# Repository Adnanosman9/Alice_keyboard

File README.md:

# Alvonomic

### This is an alice style keyboard

It has 65 keys

## Key Features
* Brain - It has a pico as braim as it has enough pins for a larg keybord
* Firmware - It usws QMK firmware built with QMK MSYS
* Keys - It has 65 keys (32 on left and 33 on right)

# Layout

This keyboard is built in Alice style. So, it has 2 sides. 

The layout was built using [Keyboard Laoyt Editor](https://www.keyboard-layout-editor.com/#/)

Compulsory sketch for this layout was geenrated with [swillkb](http://builder.swillkb.com/)

# The board

The board schematic and PCB is made in KiCAD 10. 

Tried to keep all files minimalistic and easy to understand. 

## Schematic

The schematic has all the details you need to understand it. 

Here is also a pico diagram if u need

## PCB

The board is made in PCB editor of KiCAD

The layout is arranged using [KLE Placer](https://github.com/zykrah/kicad-kle-placer) plugin

It uses Kalih hot swap socket switches footprint to make it hot swappable. 

The board has 2 layers. 

# The enclosure

The case to hold the keyboard is built using Fusion 360

This keyboard uses sandwich mount mechanism. 

The wall of the case is 5mm (2mm inner edge and 3mm outer edge) 

It has 3 parts
* Case
* Switch layer: The layer that holds the PCB hanging with switches attached
* Top layer: The layer that holds the switch layer attached with the case.

To attach all parts, I used M2 heat inserts to insert M2 screws.

## Case 

## Switch layer 

## Top Layer

# BOM

| Type | Product | Reason | Link | Number | Price (in USD) |
| :--- | :--- | :--- | :--- | :--- | ---: |
| MCU | Raspberry Pi Pico | This is the main head | [RoboticsBD](https://store.roboticsbd.com/raspberry-pi/1599-raspberry-pi-pico-robotics-bangladesh.html) | 1 | $7 |
| Switches | 3 PIN RK 35 PCS BOX SWITCH | Main switch of the keyboard | [Vibe Gaming](https://vibegaming.com.bd/product/royal-kludge-coffee-3-pin-rk-35-pcs-box-switch/) | 2 (one box has 35 switches; need 65) | $24 |
| Sockets | Kailh hot swap socket | To keep the switches safe from soldering | [KeeBD](https://keebd.com/products/kailh-mx-hotswap-sockets?srsltid=AYCX9vItRFrba52Sznx3OyVxSVSZ6HQtzewSawFc_UnNEYX08d0Pu2D8) | 7 (1 packet has 10) | $22 |
| Diodes | 1N4148 SMD - SOD 123 | For column and row connection | [Daraz](https://www.daraz.com.bd/products/100pcs-schottky-diodes-smd-diode-0805-sod-123-1n5819-1n4007-1n4148-sod123-sod-323-1206-1n4148ws-1n5819ws-b5819ws-sod323-i1613397264-s12729157906.html?) | 1 | $3 |
| PCB | JLCPCB | To hold the keys | [JLCPCB](https://jlcpcb.com/) | 1 | $44 |
| Physical parts | Locally printed | Main case | - | Case, Top, and switch layer | $10 (expected) |
| **Total** | | | | | **$110** |

# Tool summery and inspiration

This keyboard is a hobby project inspired from Unique and pretty designs of ALice style keyboards

Tools I have used
- [KiCAD](https://www.kicad.org/)
- [Fusion 360](https://www.autodesk.com/products/fusion-360/overview)
- [KLE Placer](https://github.com/zykrah/kicad-kle-placer)
- [Keyboard Laoyt Editor](https://www.keyboard-layout-editor.com/#/)
- [swillkb](http://builder.swillkb.com/)

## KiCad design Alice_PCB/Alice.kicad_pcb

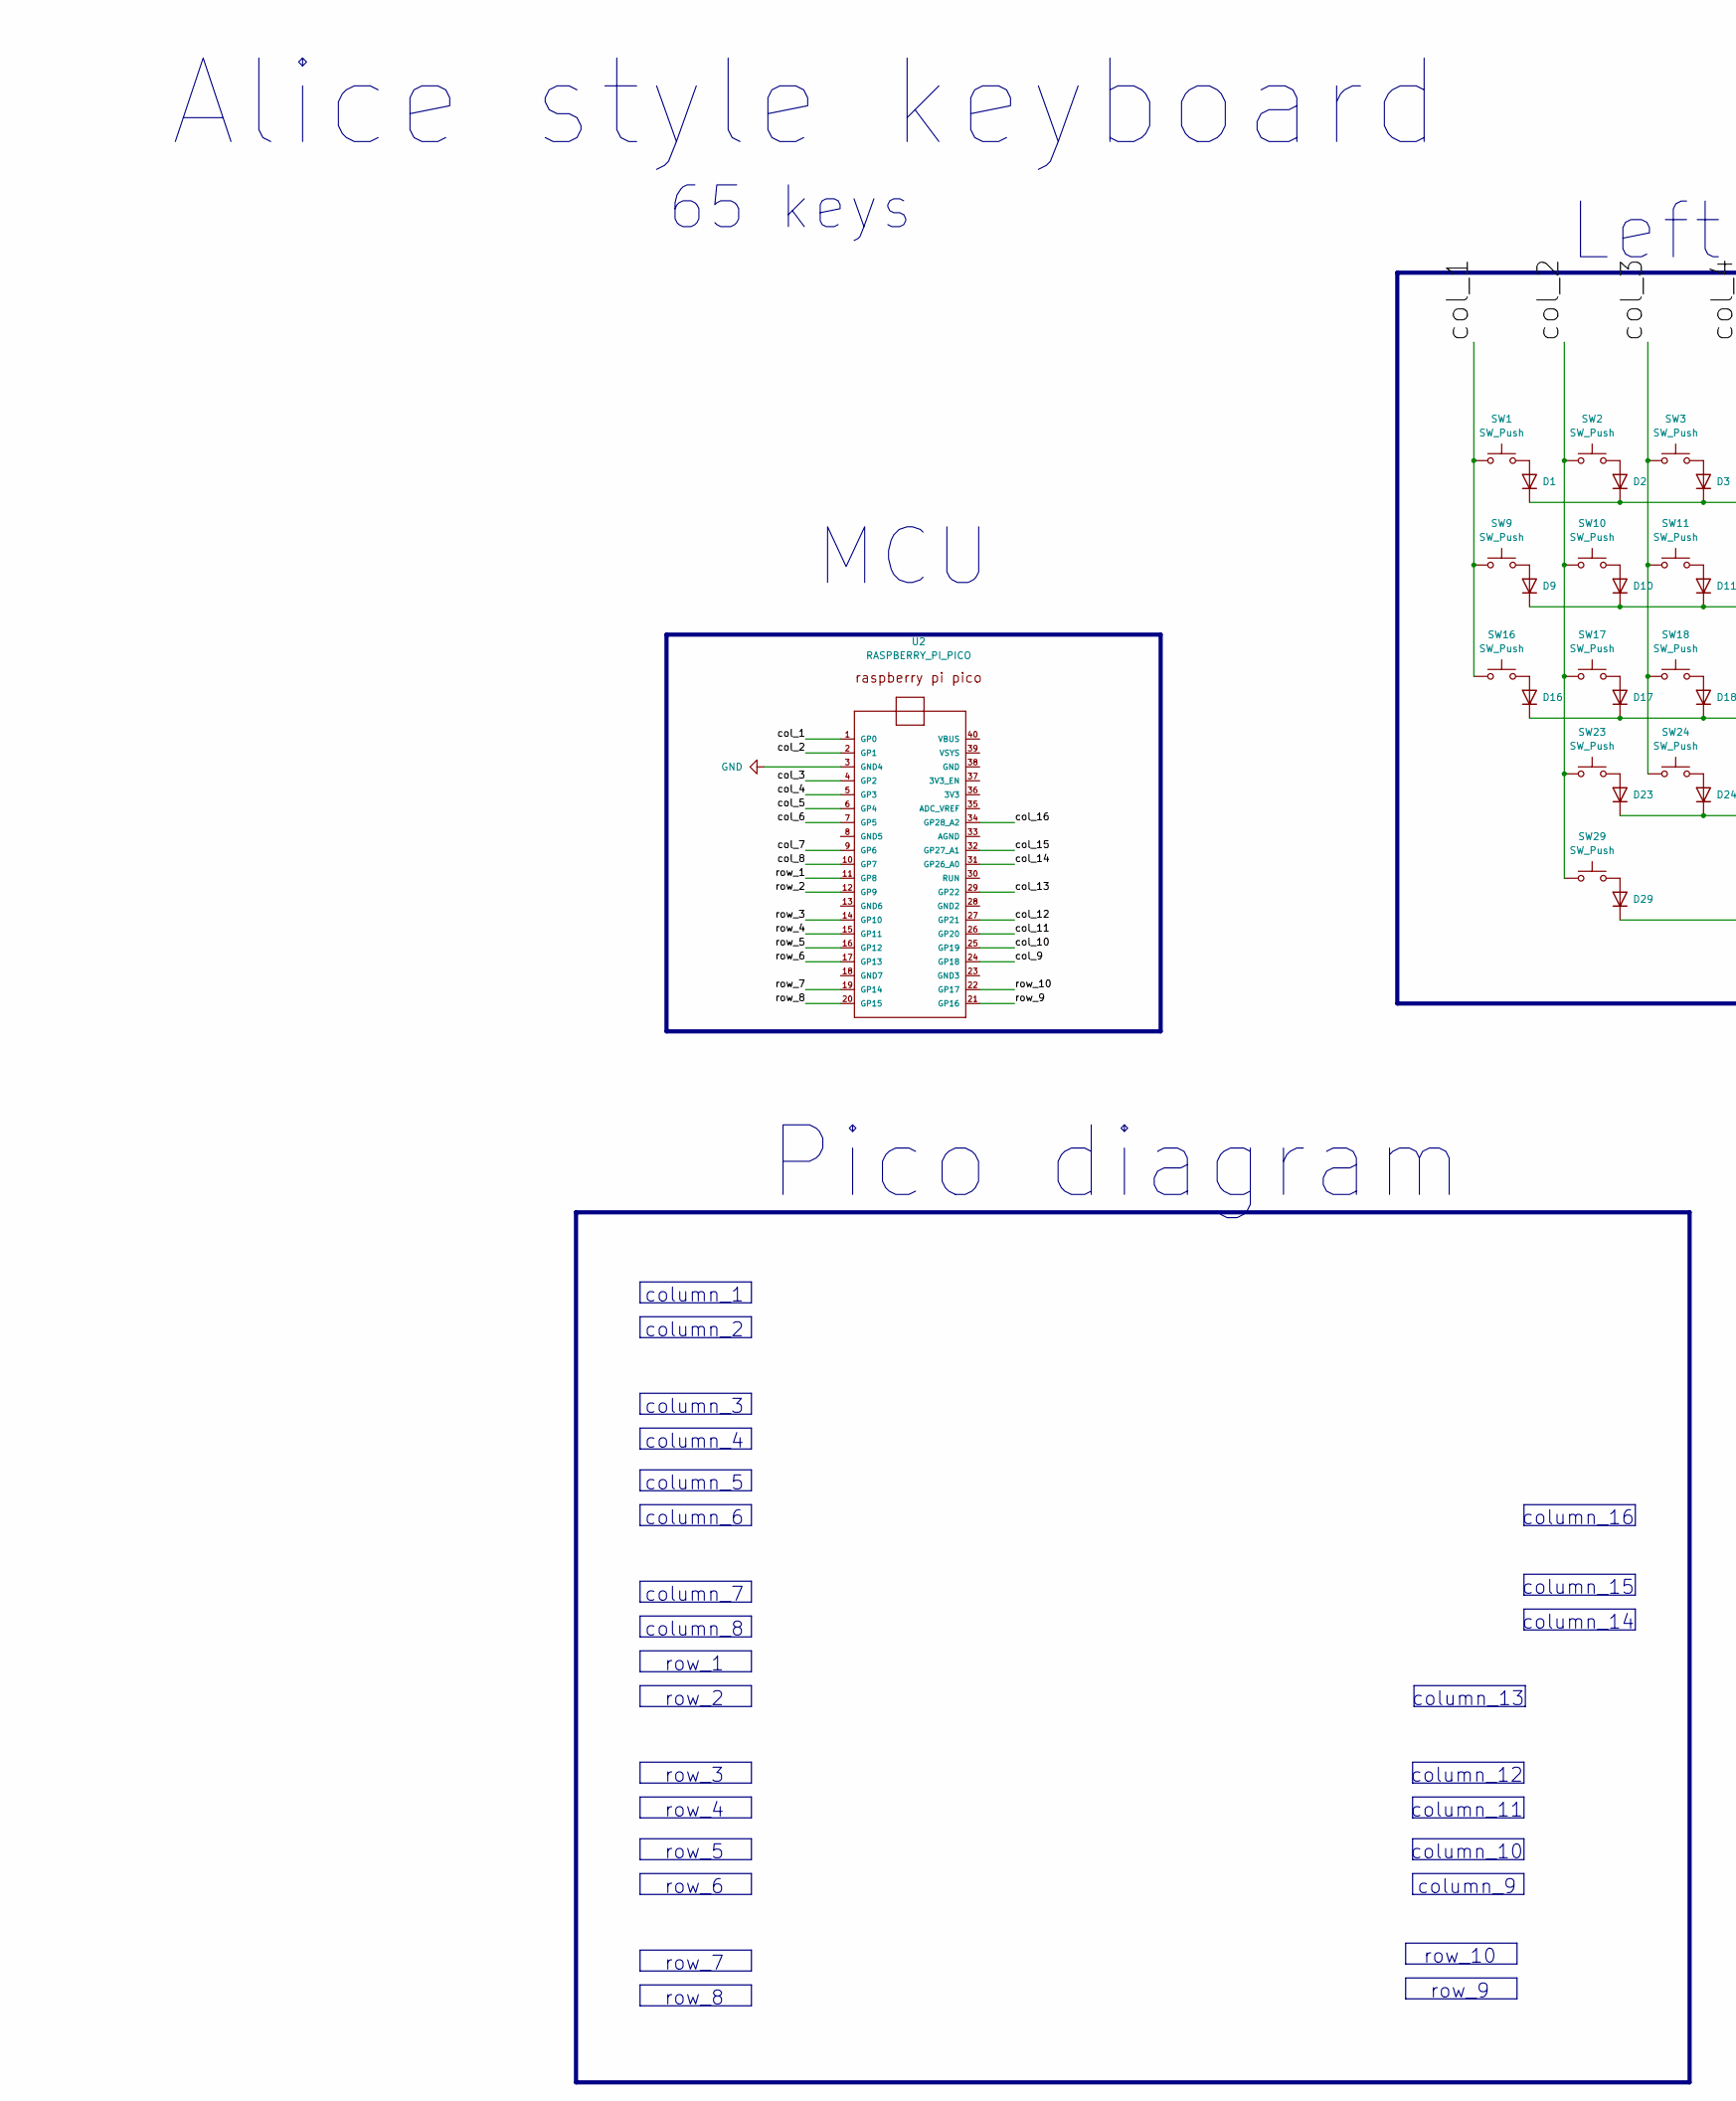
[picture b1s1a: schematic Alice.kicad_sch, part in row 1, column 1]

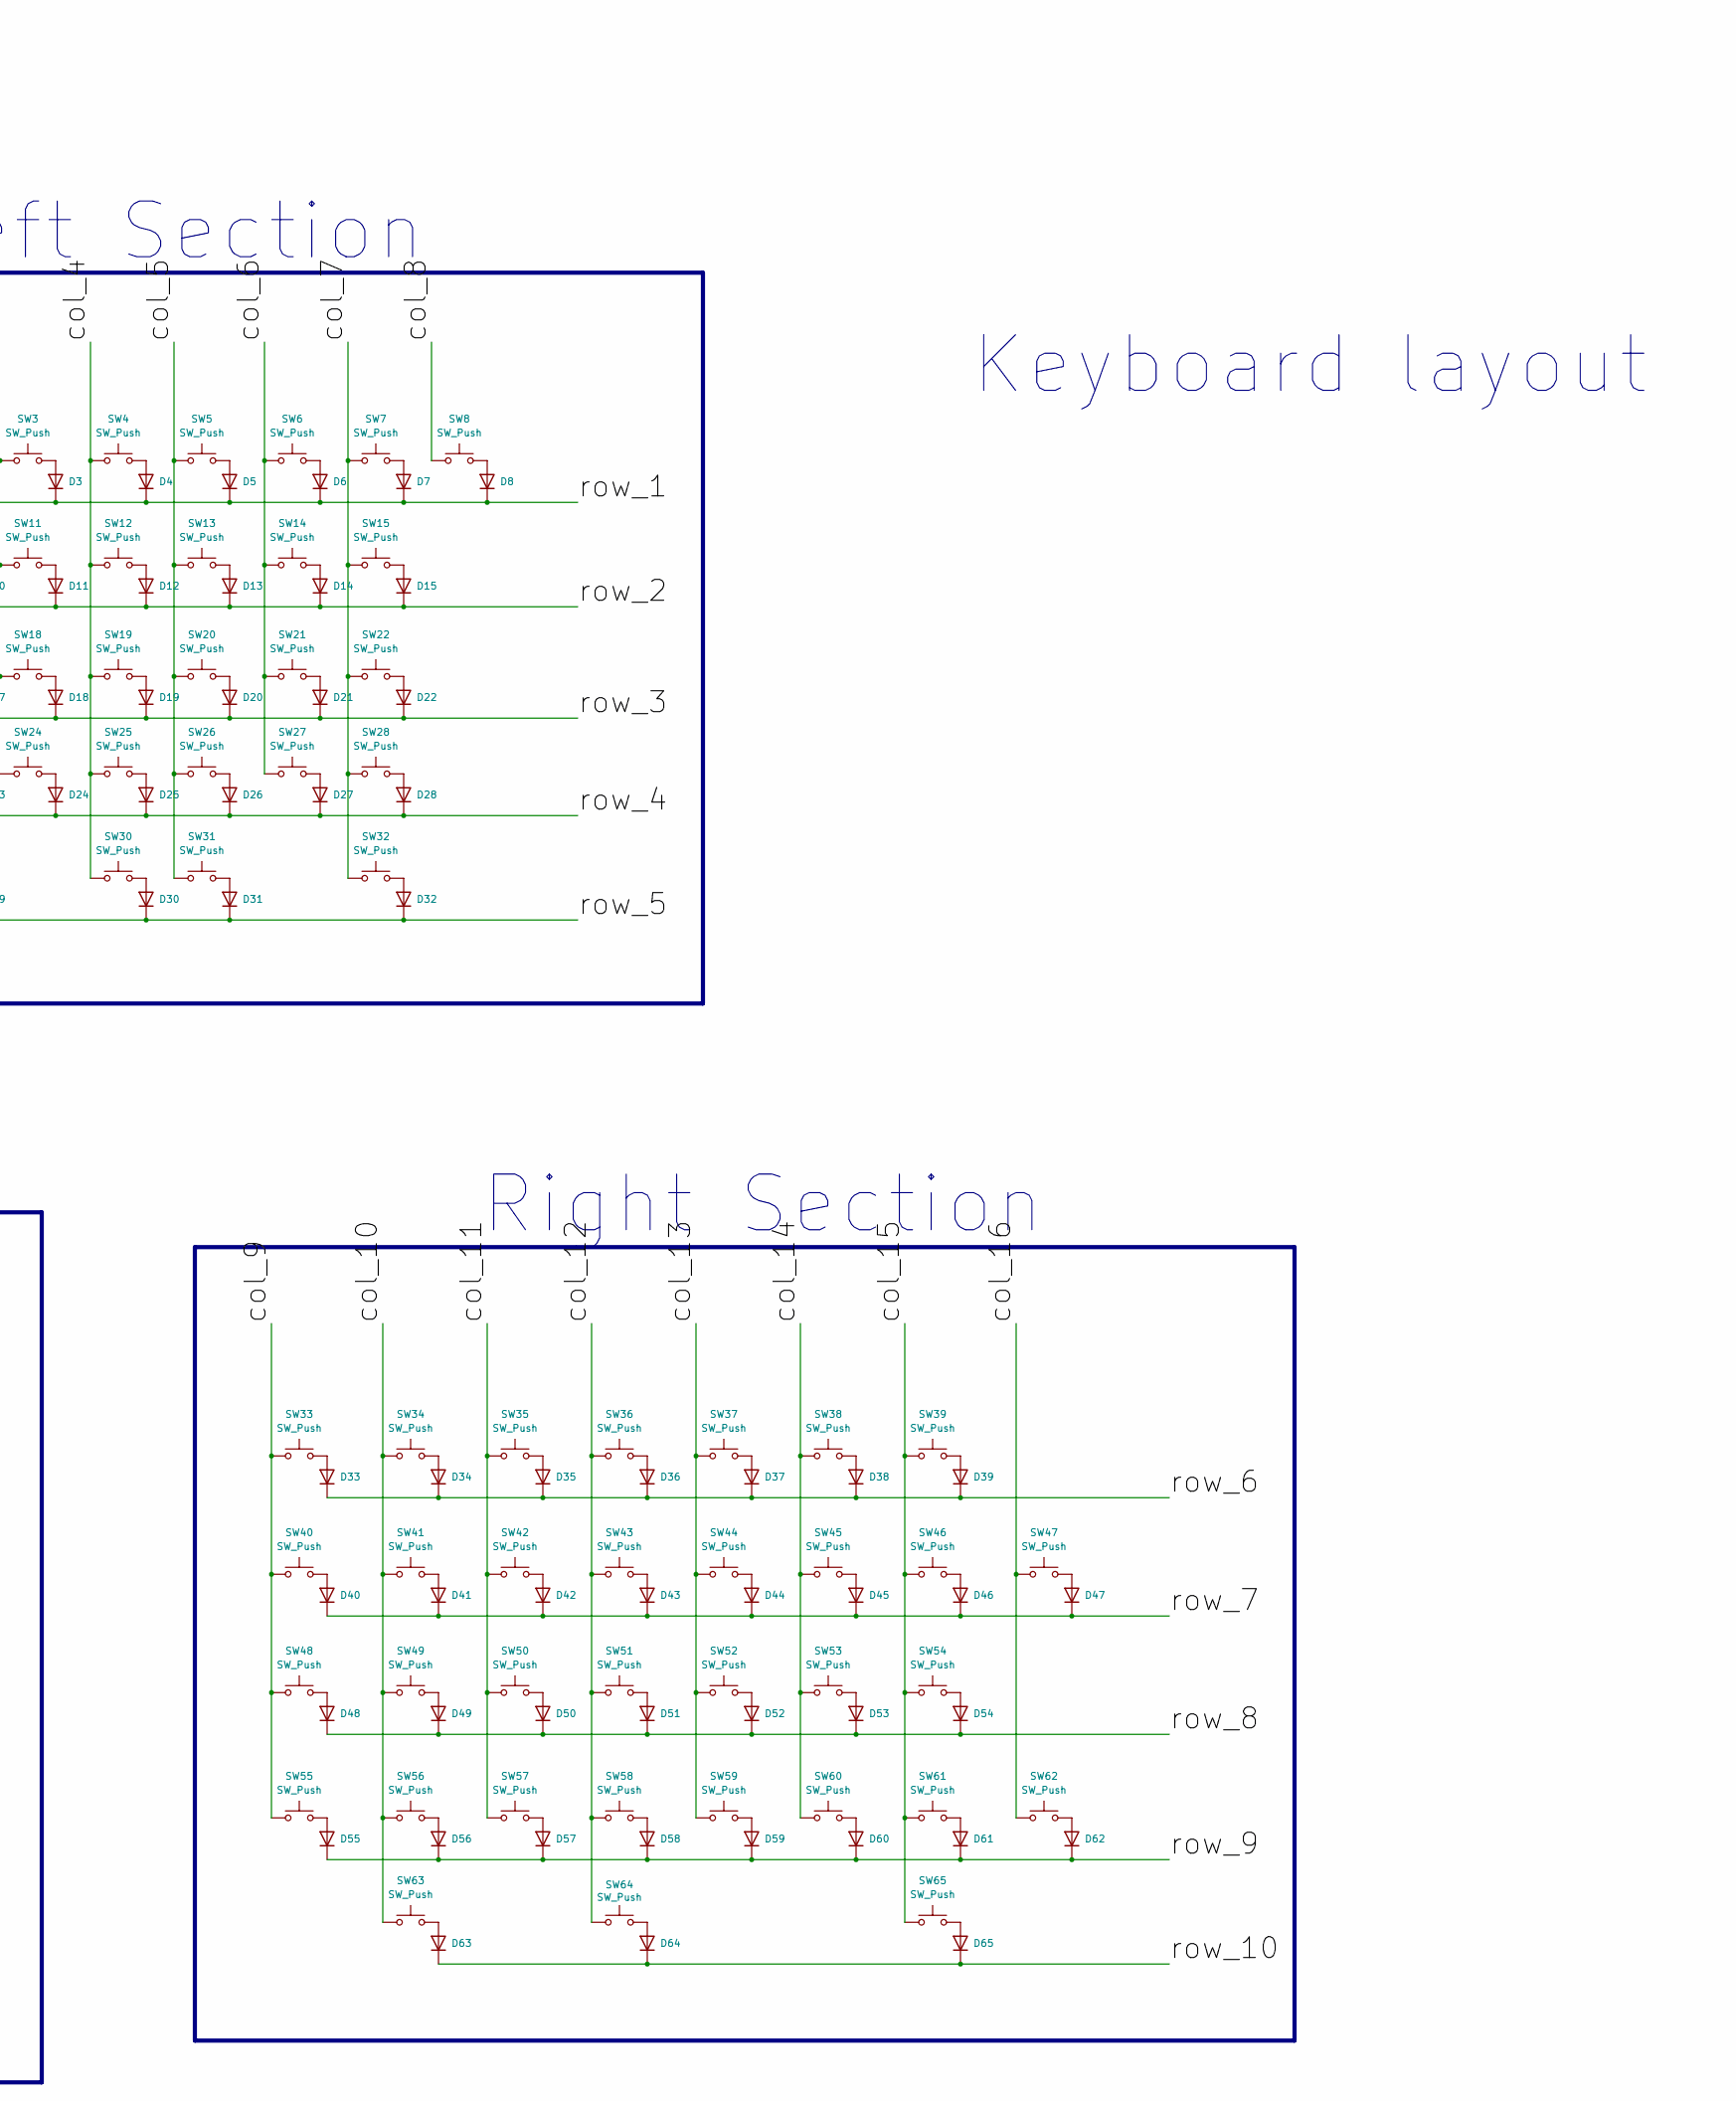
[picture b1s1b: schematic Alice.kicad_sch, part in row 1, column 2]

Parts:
D1, D2, D3, D4, D5, D6, D7, D8, D9, D10, D11, D12, D13, D14, D15, D16, D17, D18, D19, D20, D21, D22, D23, D24, D25, D26, D27, D28, D29, D30, D31, D32, D33, D34, D35, D36, D37, D38, D39, D40, D41, D42, D43, D44, D45, D46, D47, D48, D49, D50, D51, D52, D53, D54, D55, D56, D57, D58, D59, D60, D61, D62, D63, D64, D65: 1N4148; D_SOD-123
SW1, SW2, SW3, SW4, SW5, SW6, SW7, SW8, SW9, SW10, SW11, SW12, SW13, SW14, SW15, SW16, SW17, SW18, SW19, SW20, SW21, SW22, SW23, SW24, SW25, SW26, SW27, SW28, SW29, SW30, SW31, SW32, SW33, SW34, SW35, SW36, SW37, SW38, SW39, SW40, SW41, SW42, SW43, SW44, SW45, SW46, SW47, SW48, SW49, SW50, SW51, SW52, SW53, SW54, SW55, SW56, SW57, SW58, SW59, SW60, SW61, SW62, SW63, SW64, SW65: SW_Push; Kailh_socket_MX
U2: RASPBERRY_PI_PICO; RaspberryPi_Pico_Common_THT; MPN RASPBERRY PI PICO

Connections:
/col_1: SW1.1, SW9.1, SW16.1, U2.1 (GP0)
/col_2: SW2.1, SW10.1, SW17.1, SW23.1, SW29.1, U2.2 (GP1)
/col_3: SW3.1, SW11.1, SW18.1, SW24.1, U2.4 (GP2)
/col_4: SW4.1, SW12.1, SW19.1, SW25.1, SW30.1, U2.5 (GP3)
/col_5: SW5.1, SW13.1, SW20.1, SW26.1, SW31.1, U2.6 (GP4)
/col_6: SW6.1, SW14.1, SW21.1, SW27.1, U2.7 (GP5)
/col_7: SW7.1, SW15.1, SW22.1, SW28.1, SW32.1, U2.9 (GP6)
/col_8: SW8.1, U2.10 (GP7)
/col_9: SW33.1, SW40.1, SW48.1, SW55.1, U2.24 (GP18)
/col_10: SW34.1, SW41.1, SW49.1, SW56.1, SW63.1, U2.25 (GP19)
/col_11: SW35.1, SW42.1, SW50.1, SW57.1, U2.26 (GP20)
/col_12: SW36.1, SW43.1, SW51.1, SW58.1, SW64.1, U2.27 (GP21)
/col_13: SW37.1, SW44.1, SW52.1, SW59.1, U2.29 (GP22)
/col_14: SW38.1, SW45.1, SW53.1, SW60.1, U2.31 (GP26_A0)
/col_15: SW39.1, SW46.1, SW54.1, SW61.1, SW65.1, U2.32 (GP27_A1)
/col_16: SW47.1, SW62.1, U2.34 (GP28_A2)
/row_1: D1.1 (K), D2.1 (K), D3.1 (K), D4.1 (K), D5.1 (K), D6.1 (K), D7.1 (K), D8.1 (K), U2.11 (GP8)
/row_2: D9.1 (K), D10.1 (K), D11.1 (K), D12.1 (K), D13.1 (K), D14.1 (K), D15.1 (K), U2.12 (GP9)
/row_3: D16.1 (K), D17.1 (K), D18.1 (K), D19.1 (K), D20.1 (K), D21.1 (K), D22.1 (K), U2.14 (GP10)
/row_4: D23.1 (K), D24.1 (K), D25.1 (K), D26.1 (K), D27.1 (K), D28.1 (K), U2.15 (GP11)
/row_5: D29.1 (K), D30.1 (K), D31.1 (K), D32.1 (K), U2.16 (GP12)
/row_6: D33.1 (K), D34.1 (K), D35.1 (K), D36.1 (K), D37.1 (K), D38.1 (K), D39.1 (K), U2.17 (GP13)
/row_7: D40.1 (K), D41.1 (K), D42.1 (K), D43.1 (K), D44.1 (K), D45.1 (K), D46.1 (K), D47.1 (K), U2.19 (GP14)
/row_8: D48.1 (K), D49.1 (K), D50.1 (K), D51.1 (K), D52.1 (K), D53.1 (K), D54.1 (K), U2.20 (GP15)
/row_9: D55.1 (K), D56.1 (K), D57.1 (K), D58.1 (K), D59.1 (K), D60.1 (K), D61.1 (K), D62.1 (K), U2.21 (GP16)
/row_10: D63.1 (K), D64.1 (K), D65.1 (K), U2.22 (GP17)
GND: U2.3 (GND4)
unnamed: D1.2 (A), SW1.2
unnamed: D2.2 (A), SW2.2
unnamed: D3.2 (A), SW3.2
unnamed: D4.2 (A), SW4.2
unnamed: D5.2 (A), SW5.2
unnamed: D6.2 (A), SW6.2
unnamed: D7.2 (A), SW7.2
unnamed: D8.2 (A), SW8.2
unnamed: D9.2 (A), SW9.2
unnamed: D10.2 (A), SW10.2
unnamed: D11.2 (A), SW11.2
unnamed: D12.2 (A), SW12.2
unnamed: D13.2 (A), SW13.2
unnamed: D14.2 (A), SW14.2
unnamed: D15.2 (A), SW15.2
unnamed: D16.2 (A), SW16.2
unnamed: D17.2 (A), SW17.2
unnamed: D18.2 (A), SW18.2
unnamed: D19.2 (A), SW19.2
unnamed: D20.2 (A), SW20.2
unnamed: D21.2 (A), SW21.2
unnamed: D22.2 (A), SW22.2
unnamed: D23.2 (A), SW23.2
unnamed: D24.2 (A), SW24.2
unnamed: D25.2 (A), SW25.2
unnamed: D26.2 (A), SW26.2
unnamed: D27.2 (A), SW27.2
unnamed: D28.2 (A), SW28.2
unnamed: D29.2 (A), SW29.2
unnamed: D30.2 (A), SW30.2
unnamed: D31.2 (A), SW31.2
unnamed: D32.2 (A), SW32.2
unnamed: D33.2 (A), SW33.2
unnamed: D34.2 (A), SW34.2
unnamed: D35.2 (A), SW35.2
unnamed: D36.2 (A), SW36.2
unnamed: D37.2 (A), SW37.2
unnamed: D38.2 (A), SW38.2
unnamed: D39.2 (A), SW39.2
unnamed: D40.2 (A), SW40.2
unnamed: D41.2 (A), SW41.2
unnamed: D42.2 (A), SW42.2
unnamed: D43.2 (A), SW43.2
unnamed: D44.2 (A), SW44.2
unnamed: D45.2 (A), SW45.2
unnamed: D46.2 (A), SW46.2
unnamed: D47.2 (A), SW47.2
unnamed: D48.2 (A), SW48.2
unnamed: D49.2 (A), SW49.2
unnamed: D50.2 (A), SW50.2
unnamed: D51.2 (A), SW51.2
unnamed: D52.2 (A), SW52.2
unnamed: D53.2 (A), SW53.2
unnamed: D54.2 (A), SW54.2
unnamed: D55.2 (A), SW55.2
unnamed: D56.2 (A), SW56.2
unnamed: D57.2 (A), SW57.2
unnamed: D58.2 (A), SW58.2
unnamed: D59.2 (A), SW59.2
unnamed: D60.2 (A), SW60.2
unnamed: D61.2 (A), SW61.2
unnamed: D62.2 (A), SW62.2
unnamed: D63.2 (A), SW63.2
unnamed: D64.2 (A), SW64.2
unnamed: D65.2 (A), SW65.2

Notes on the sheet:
Pico diagram
row_8
column_12
column_14
row_4
row_2
column_11
column_1
column_15
65 keys
column_8
column_7
row_1
Right Section
column_4
column_16
Alice style keyboard
row_9
row_10
column_6
column_2
row_3
Keyboard layout
row_5
row_7
column_5
column_10
MCU
row_6
column_3
column_13
Left Section
column_9

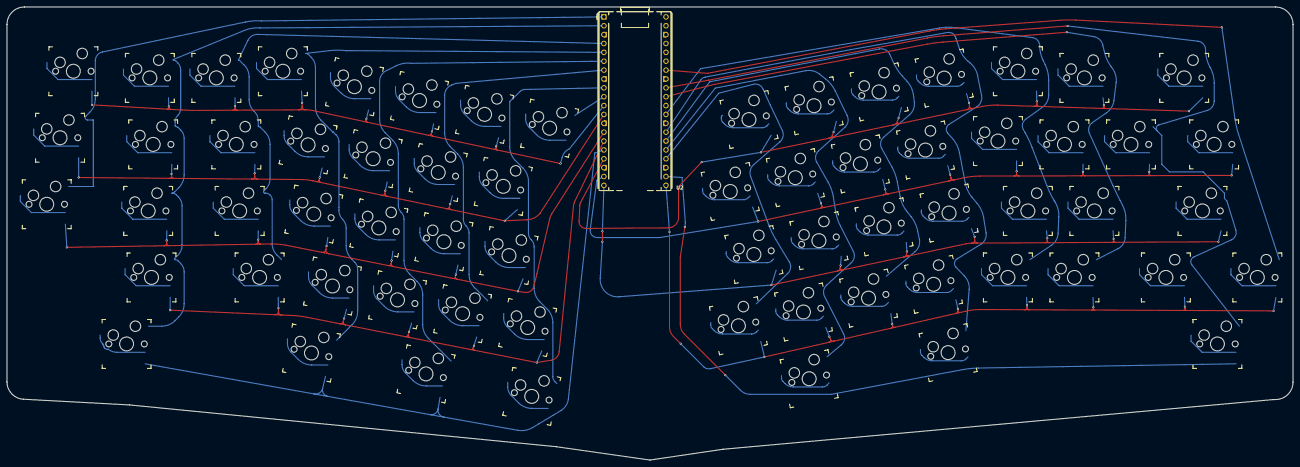
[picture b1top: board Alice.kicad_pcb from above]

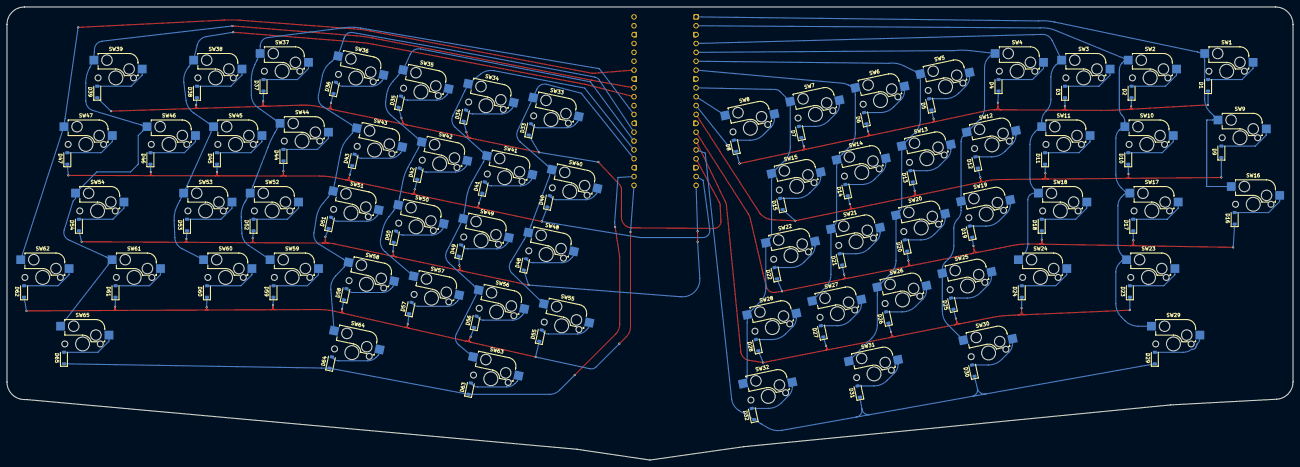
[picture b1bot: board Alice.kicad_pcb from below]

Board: 2 copper layers, 368.3 x 129.8 mm, 131 parts (65 on the bottom side), 91 nets.
